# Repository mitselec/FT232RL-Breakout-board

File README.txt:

Breakout board for the FT232RL chip

Initially designed by Costas Efstathiou in Protell 99
Designed by Dimitrios Dimopoulos in Eagle

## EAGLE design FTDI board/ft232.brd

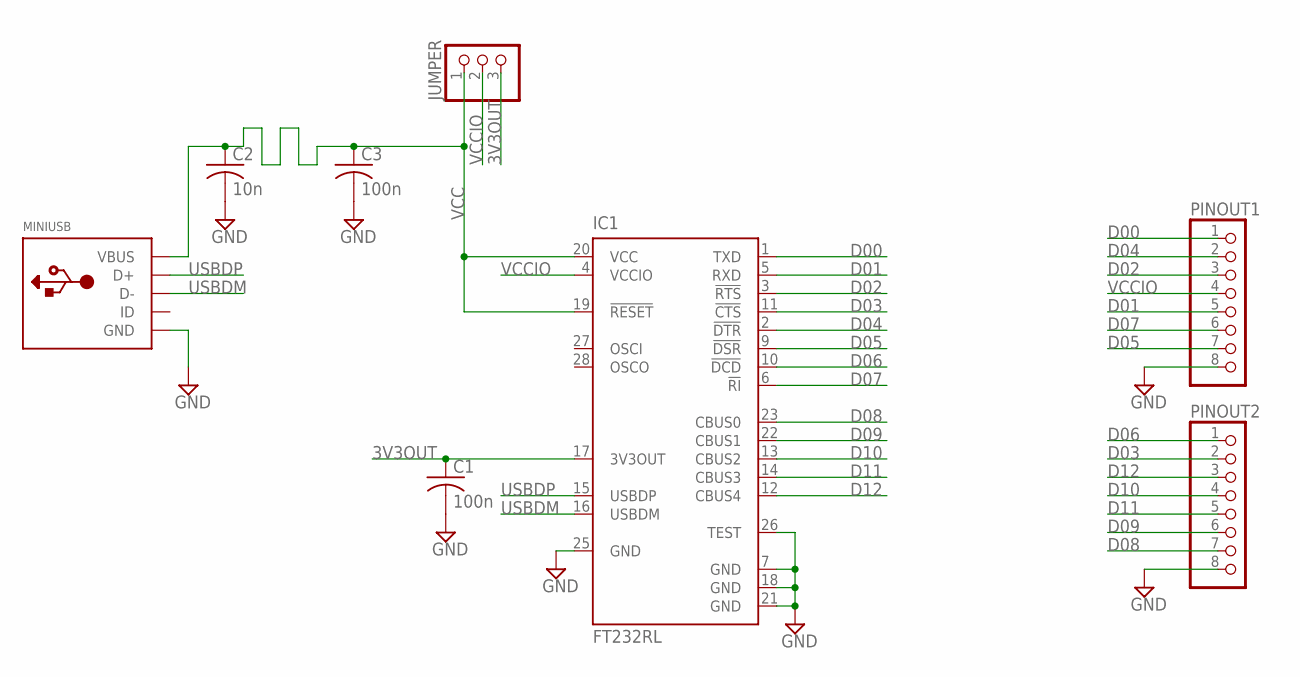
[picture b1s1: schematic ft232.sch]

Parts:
C1, C3: 100n; C0805
C2: 10n; C0805
IC1: FT232RL; SSOP28
JUMPER: PINHD-1X3CB; 1X03-CLEANBIG
MINIUSB: USBMINIB; USB-MINIB
PINOUT1, PINOUT2: PINHD-1X8; 1X08

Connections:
3V3OUT: C1.1, IC1.17 (3V3OUT), JUMPER.3
D00: IC1.1 (TXD), PINOUT1.1
D01: IC1.5 (RXD), PINOUT1.5
D02: IC1.3 (!RTS), PINOUT1.3
D03: IC1.11 (!CTS), PINOUT2.2
D04: IC1.2 (!DTR), PINOUT1.2
D05: IC1.9 (!DSR), PINOUT1.7
D06: IC1.10 (!DCD), PINOUT2.1
D07: IC1.6 (!RI), PINOUT1.6
D08: IC1.23 (CBUS0), PINOUT2.7
D09: IC1.22 (CBUS1), PINOUT2.6
D10: IC1.13 (CBUS2), PINOUT2.4
D11: IC1.14 (CBUS3), PINOUT2.5
D12: IC1.12 (CBUS4), PINOUT2.3
GND: C1.2, C2.2, C3.2, IC1.7 (GND), IC1.18 (GND), IC1.21 (GND), IC1.25 (GND), IC1.26 (TEST), MINIUSB.GND, PINOUT1.8, PINOUT2.8
USBDM: IC1.16 (USBDM), MINIUSB.D-
USBDP: IC1.15 (USBDP), MINIUSB.D+
VCC: C2.1, C3.1, IC1.19 (!RESET), IC1.20 (VCC), JUMPER.1, MINIUSB.VBUS
VCCIO: IC1.4 (VCCIO), JUMPER.2, PINOUT1.4

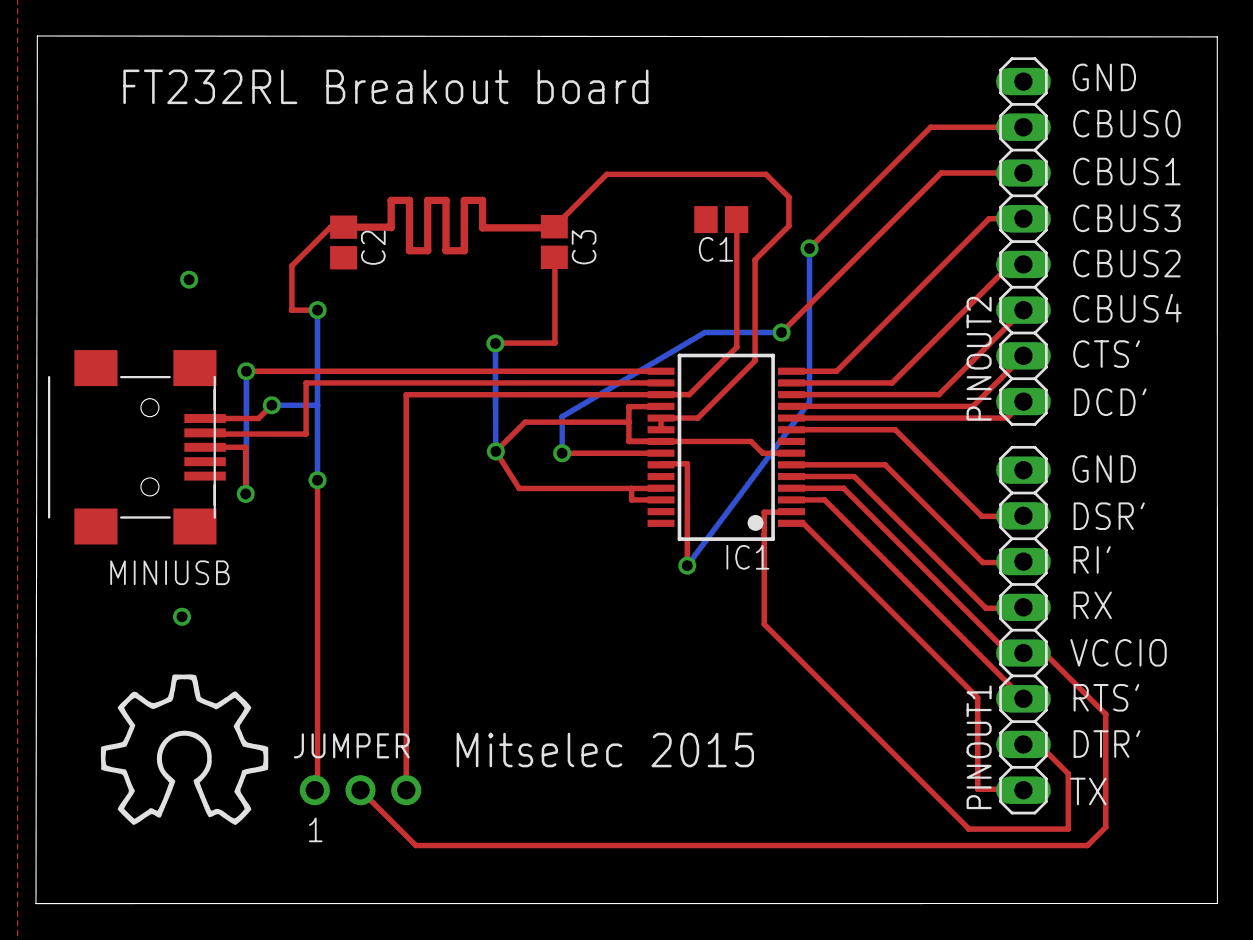
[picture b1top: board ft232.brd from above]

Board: 2 copper layers, 65.6 x 48.2 mm, 8 parts (0 on the bottom side), 19 nets.

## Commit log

2015-09-12 :tada: Added .gitattributes & .gitignore files
2015-09-12 FT232RL Breakout Board
    A breakout board for the FT232RL chip
